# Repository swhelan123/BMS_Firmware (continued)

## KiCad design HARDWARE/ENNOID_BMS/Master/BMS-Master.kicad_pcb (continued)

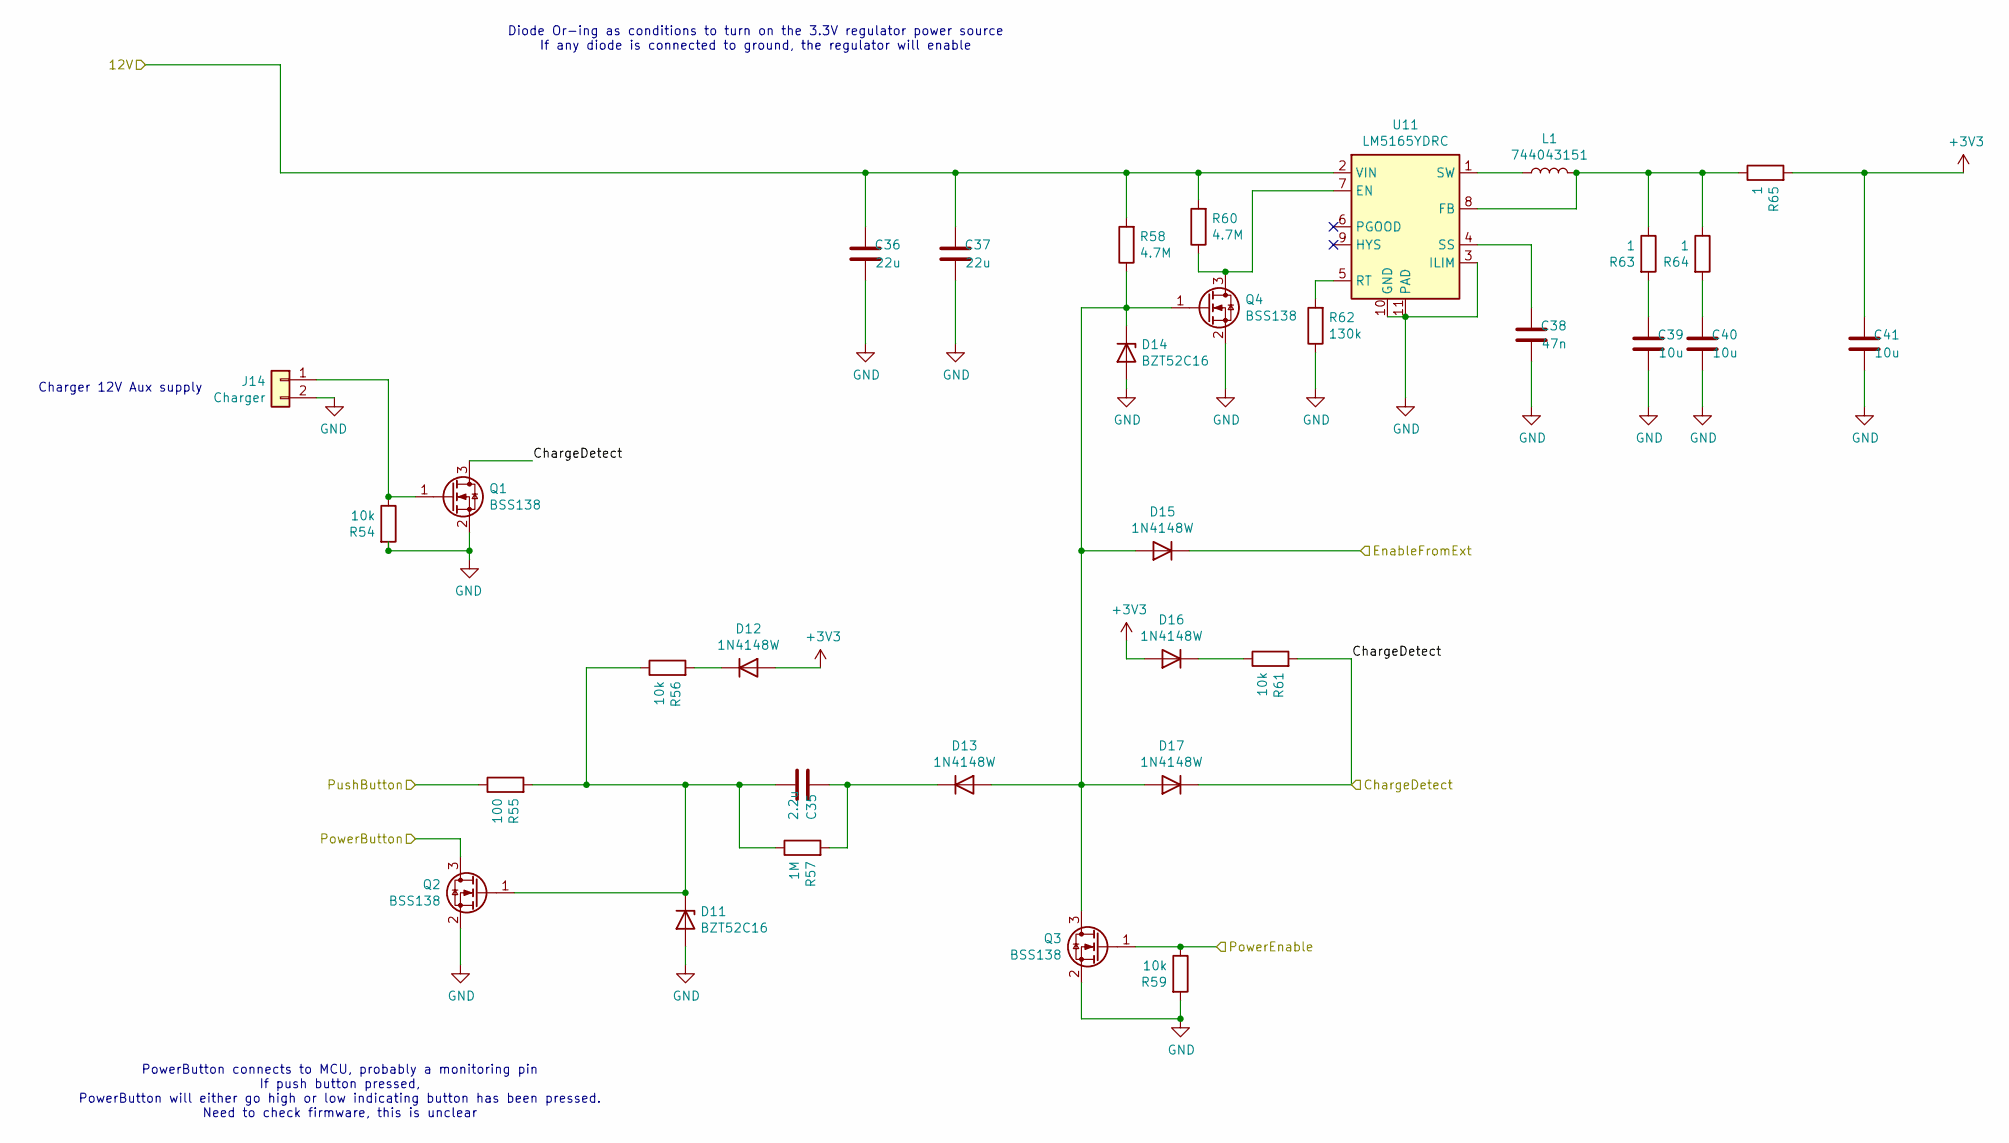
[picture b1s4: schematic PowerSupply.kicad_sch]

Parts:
C35: 2.2u; C_0603_1608Metric; MPN GRM188R61A225KE34D
C36, C37: 22u; C_0805_2012Metric; MPN CL21A226MOQNNNE
C38: 47n; C_0603_1608Metric; Voltage 100V; MPN GCM188R71H473KA55D
C39, C40, C41: 10u; C_0603_1608Metric; MPN CL10A106MQ8NNNC
D11, D14: BZT52C16; D_SOD-123; MPN BZT52C16-E3-08
D12, D13, D15, D16, D17: 1N4148W; D_SOD-123; MPN 1N4148W-7-F
J14: Charger; JST_XH_B2B-XH-A_1x02_P2.50mm_Vertical; MPN B2B-XH-A
L1: 744043151; L_Wuerth_WE-PD2-Typ-MS; MPN 744043151
Q1, Q2, Q3, Q4: BSS138; SOT-23; MPN BSS138
R54, R56, R59, R61: 10k; R_0603_1608Metric; MPN RC0603FR-0710KL
R55: 100; R_0603_1608Metric; MPN RC0603FR-07100RL
R57: 1M; R_0603_1608Metric; MPN RC0603JR-071ML
R58, R60: 4.7M; R_0603_1608Metric; MPN RC0603FR-074M7L
R62: 130k; R_0603_1608Metric; MPN RC0603FR-07130KL
R63, R64, R65: 1; R_0603_1608Metric; MPN RC0603FR-071RL
U11: LM5165YDRC; Texas_S-PVSON-N10_ThermalVias; MPN LM5165YDRCT

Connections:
+3V3: C41.2, D12.2 (A), D16.2 (A), R65.2; also elsewhere on the board
+12V: C36.2, C37.2, R58.2, R60.2, U11.2 (VIN); also elsewhere on the board
/CAN/EnableRequest: D15.1 (K); also elsewhere on the board
/MCU/PowerButton: Q2.3 (D); also elsewhere on the board
/MCU/PowerEnable: Q3.1 (G), R59.1; also elsewhere on the board
/PowerSupply/ChargeDetect: D17.1 (K), Q1.3 (D), R61.2; also elsewhere on the board
/PowerSupply/PushButton: R55.1; also elsewhere on the board
GND: C36.1, C37.1, C38.1, C39.1, C40.1, C41.1, D11.2 (A), D14.2 (A), J14.2, Q1.2 (S), Q2.2 (S), Q3.2 (S), Q4.2 (S), R54.2, R59.2, R62.1, U11.3 (ILIM), U11.10 (GND), U11.11 (PAD); also elsewhere on the board
unnamed: C39.2, R63.2
unnamed: C40.2, R64.2
unnamed: C35.1, D11.1 (K), Q2.1 (G), R55.2, R56.1, R57.1
unnamed: D12.1 (K), R56.2
unnamed: D13.2 (A), D14.1 (K), D15.2 (A), D17.2 (A), Q3.3 (D), Q4.1 (G), R58.1
unnamed: C35.2, D13.1 (K), R57.2
unnamed: D16.1 (K), R61.1
unnamed: J14.1, Q1.1 (G), R54.1
unnamed: Q4.3 (D), R60.1, U11.7 (EN)
unnamed: L1.2, R63.1, R64.1, R65.1, U11.8 (FB)
unnamed: R62.2, U11.5 (RT)
unnamed: C38.2, U11.4 (SS)
unnamed: L1.1, U11.1 (SW)

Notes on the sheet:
Diode Or-ing as conditions to turn on the 3.3V regulator power source If any diode is connected to ground, the regulator will enable
PowerButton connects to MCU, probably a monitoring pin If push button pressed, PowerButton will either go high or low indicating button has been pressed. Need to check firmware, this is unclear
Charger 12V Aux supply

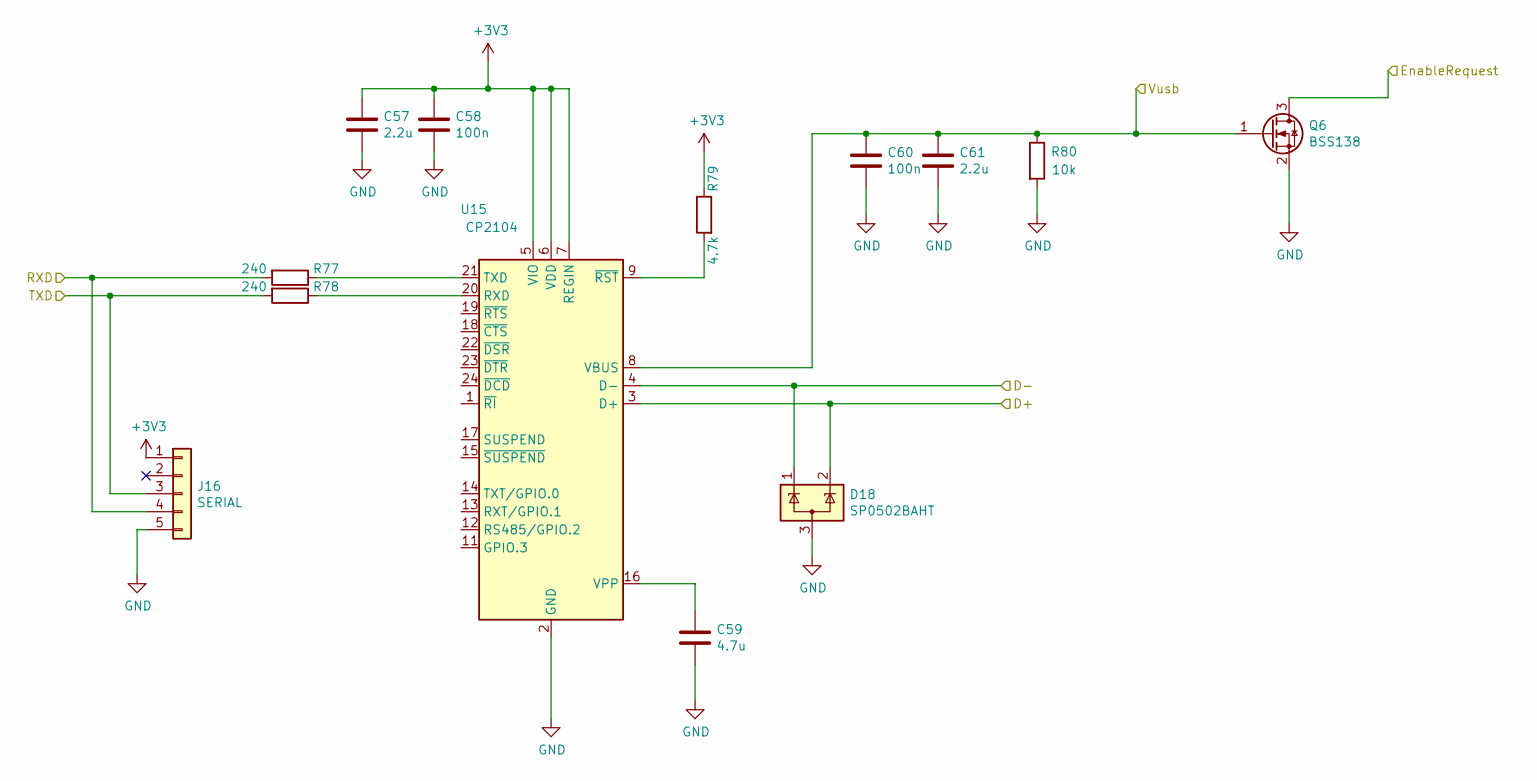
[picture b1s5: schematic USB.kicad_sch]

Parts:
C57, C61: 2.2u; C_0603_1608Metric; MPN GRM188R61A225KE34D
C58, C60: 100n; C_0603_1608Metric; MPN GRM188R71E104KA01D
C59: 4.7u; C_0603_1608Metric; MPN GRM188Z71A475ME15D
D18: SP0502BAHT; SOT-23; MPN SP0502BAHTG
J16: SERIAL; JST_XH_B5B-XH-A_1x05_P2.50mm_Vertical; MPN B5B-XH-A
Q6: BSS138; SOT-23; MPN BSS138
R77, R78: 240; R_0603_1608Metric; MPN RC0603FR-07240RL
R79: 4.7k; R_0603_1608Metric; MPN RC0603JR-074K7L
R80: 10k; R_0603_1608Metric; MPN RC0603FR-0710KL
U15: CP2104; QFN-24-1EP_4x4mm_P0.5mm_EP2.7x2.7mm; MPN CP2104-F03-GM

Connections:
+3V3: C57.1, C58.1, J16.1, R79.1, U15.5 (VIO), U15.6 (VDD), U15.7 (REGIN); also elsewhere on the board
/CAN/EnableRequest: Q6.3 (D); also elsewhere on the board
/MCU/RX_USB: J16.4, R77.2; also elsewhere on the board
/MCU/TX_USB: J16.3, R78.2; also elsewhere on the board
/USB/D+: D18.2 (K), U15.3 (D+); also elsewhere on the board
/USB/D-: D18.1 (K), U15.4 (D-); also elsewhere on the board
/USB/Vusb: C60.1, C61.1, Q6.1 (G), R80.1, U15.8 (VBUS); also elsewhere on the board
GND: C57.2, C58.2, C59.2, C60.2, C61.2, D18.3 (A), J16.5, Q6.2 (S), R80.2, U15.2 (GND), U15.25 (GND); also elsewhere on the board
unnamed: R78.1, U15.20 (RXD)
unnamed: R77.1, U15.21 (TXD)
unnamed: C59.1, U15.16 (VPP)
unnamed: R79.2, U15.9 (~RST)

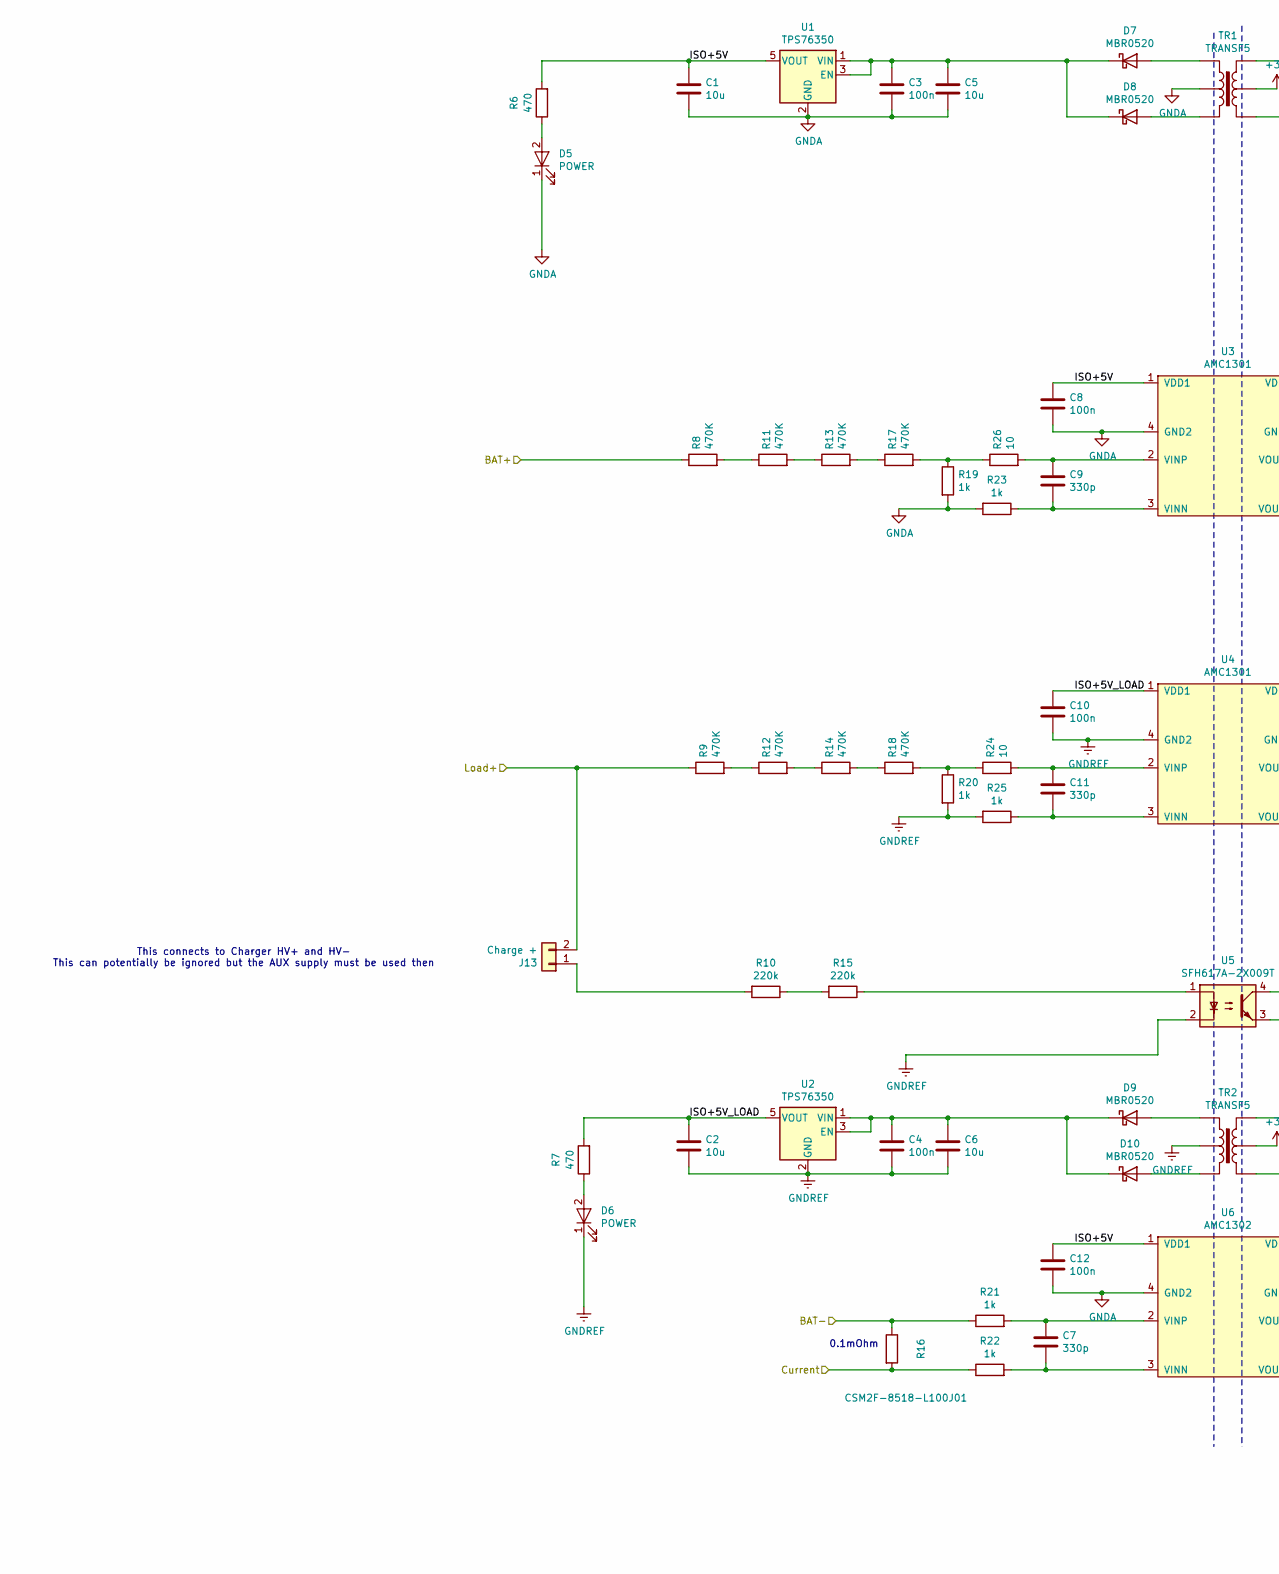
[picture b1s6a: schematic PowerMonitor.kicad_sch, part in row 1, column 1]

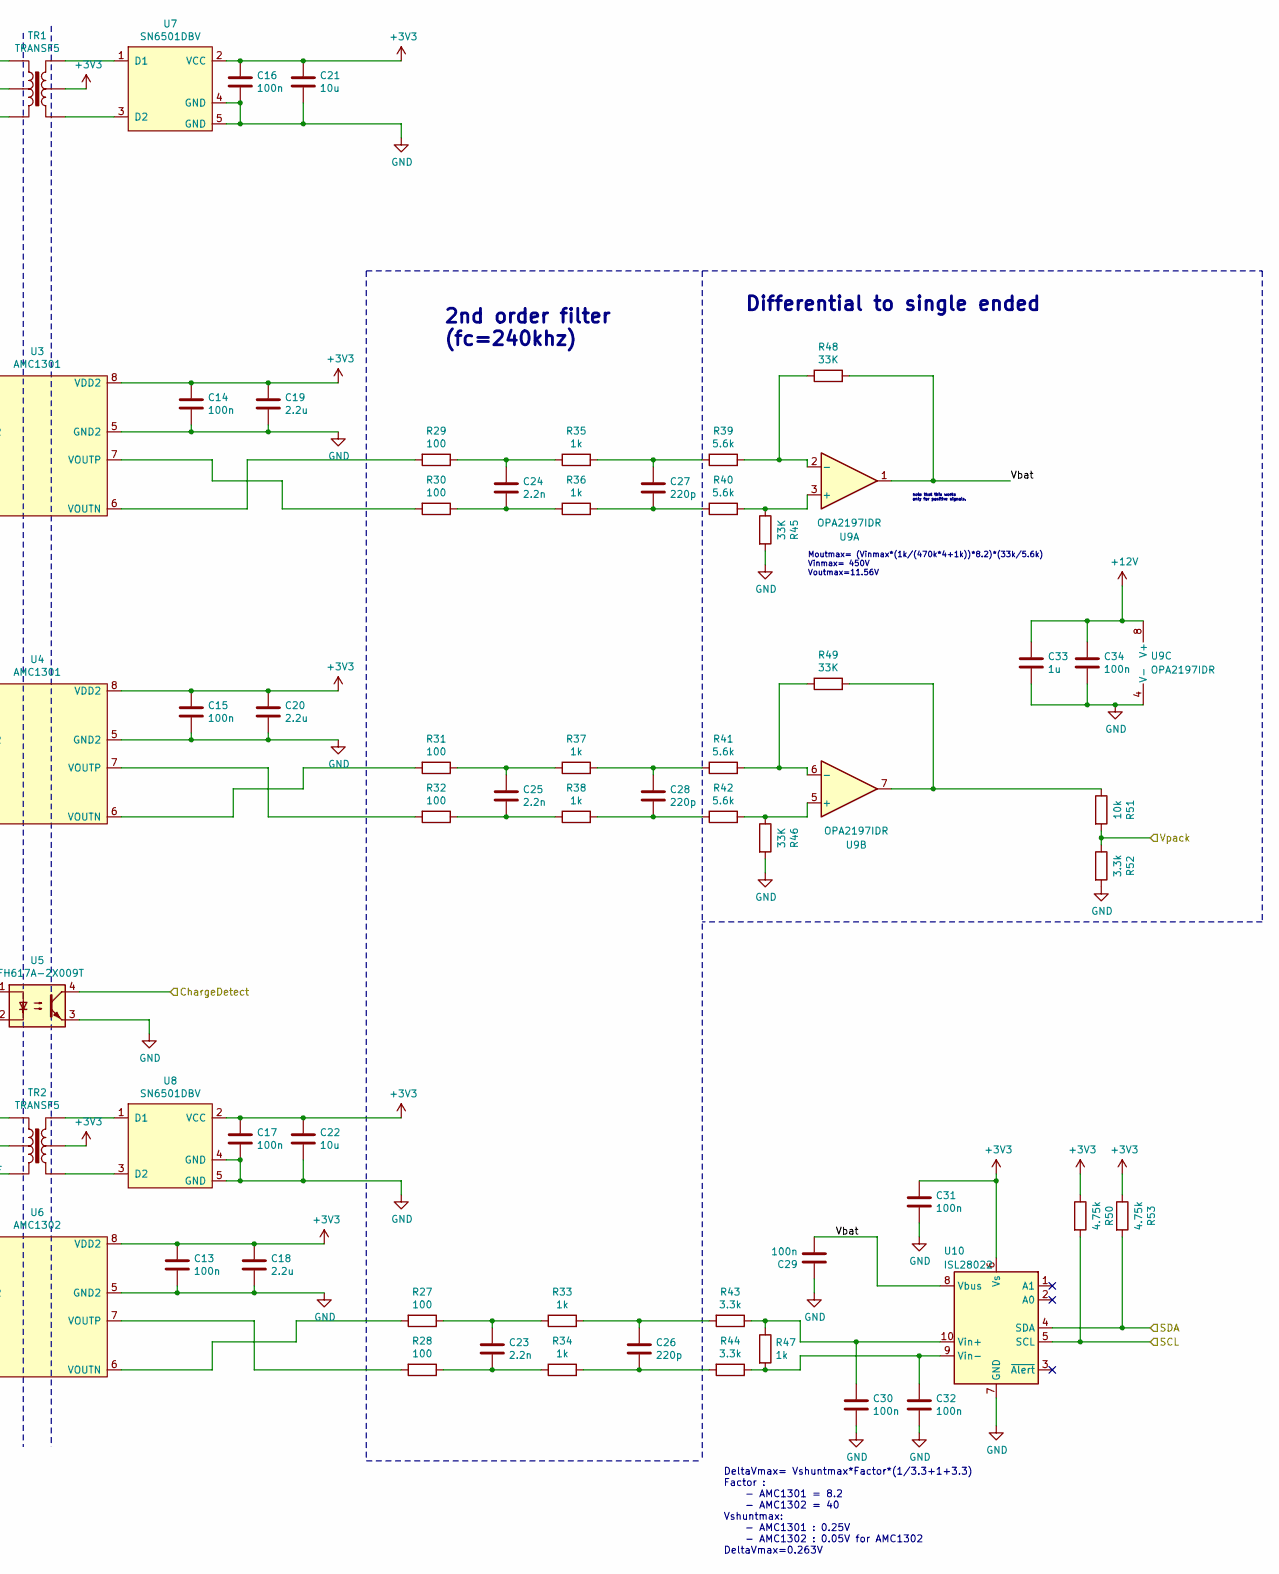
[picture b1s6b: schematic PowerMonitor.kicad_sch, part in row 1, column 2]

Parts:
C1, C2, C5, C6: 10u; C_0805_2012Metric; MPN CL21A106KAYNNNE
C3, C4, C8, C10, C12, C13, C14, C15, C16, C17, C29, C30, C31, C32, C34: 100n; C_0603_1608Metric; MPN GRM188R71E104KA01D
C7, C9, C11: 330p; C_0603_1608Metric; MPN CL10B331KB8NNNC
C18, C19, C20: 2.2u; C_0603_1608Metric; MPN GRM188R61A225KE34D
C21, C22: 10u; C_0603_1608Metric; MPN CL10A106MQ8NNNC
C23, C24, C25: 2.2n; C_0603_1608Metric; MPN GRM1885C1H222JA01D
C26, C27, C28: 220p; C_0603_1608Metric; MPN GRM1555C1H221JA01D
C33: 1u; C_0603_1608Metric; MPN GRM188R71E105KA12D
D5, D6: POWER; LED_0603_1608Metric; MPN SML-D12P8WT86C
D7, D8, D9, D10: MBR0520; D_SOD-123; MPN MBR0502L
J13: Charge +; Phoenix_1x2_1729128; MPN 1729128
R6, R7: 470; R_0603_1608Metric; MPN RC0603JR-07470RL
R8, R9, R11, R12, R13, R14, R17, R18: 470K; R_1206_3216Metric; MPN RC1206FR-07470KL
R10, R15: 220k; R_2512_6332Metric; MPN CRCW2512220KFKEG
R16: CSM2F-8518-L100J01; MPN CSM2F-8518-L100J01
R19, R20, R21, R22, R23, R25, R33, R34, R35, R36, R37, R38, R47: 1k; R_0603_1608Metric; MPN MCWR06X1001FTL
R24, R26: 10; R_0603_1608Metric; MPN RC0603JR-0710RL
R27, R28, R29, R30, R31, R32: 100; R_0603_1608Metric; MPN RC0603FR-07100RL
R39, R40, R41, R42: 5.6k; R_0603_1608Metric; MPN RC0603JR-075K6L
R43, R44, R52: 3.3k; R_0603_1608Metric; MPN RC0603FR-073K3L
R45, R46, R48, R49: 33K; R_0603_1608Metric; MPN RC0603FR-0733KL
R50, R53: 4.75k; R_0603_1608Metric; MPN RC0603JR-074K7L
R51: 10k; R_0603_1608Metric; MPN RC0603FR-0710KL
TR1, TR2: TRANSF5; WURTH-760390014; MPN 760390014
U1, U2: TPS76350; SOT-23-5; MPN TPS76350DBVR
U3, U4: AMC1301; SSO-8_6.8x5.9mm_Pitch1.27mm_Clearance8mm; MPN AMC1301DWV
U5: SFH617A-2X009T; SMDIP-4_W9.53mm_Clearance8mm; MPN SFH617A-2X009T
U6: AMC1302; SSO-8_6.8x5.9mm_Pitch1.27mm_Clearance8mm; MPN AMC1302
U7, U8: SN6501DBV; SOT-23-5; MPN SN6501DBVR
U9: OPA2197IDR; SOIC-8_3.9x4.9mm_P1.27mm; MPN OPA2197IDR
U10: ISL28022; MSOP-10_3x3mm_P0.5mm; MPN ISL28022FUZ-T7A

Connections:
+3V3: C13.1, C14.1, C15.1, C16.1, C17.1, C18.1, C19.1, C20.1, C21.1, C22.1, C31.2, R50.1, R53.1, TR1.5, TR2.5, U3.8 (VDD2), U4.8 (VDD2), U6.8 (VDD2), U7.2 (VCC), U8.2 (VCC), U10.6 (Vs); also elsewhere on the board
+12V: C33.1, C34.1, U9.8 (V+); also elsewhere on the board
/BAT+: R8.1; also elsewhere on the board
/Load+: J13.2, R9.1; also elsewhere on the board
/MCU/SCL: R50.2, U10.5 (SCL); also elsewhere on the board
/MCU/SDA: R53.2, U10.4 (SDA); also elsewhere on the board
/MCU/Vpack: R51.2, R52.1; also elsewhere on the board
/PowerMonitor/Current: R16.2, R22.1; also elsewhere on the board
/PowerMonitor/ISO+5V: C1.1, C8.1, C12.1, R6.2, U1.5 (VOUT), U3.1 (VDD1), U6.1 (VDD1)
/PowerMonitor/ISO+5V_LOAD: C2.1, C10.1, R7.2, U2.5 (VOUT), U4.1 (VDD1)
/PowerMonitor/Vbat: C29.1, R48.2, U9.1, U10.8 (Vbus)
/PowerSupply/ChargeDetect: U5.4; also elsewhere on the board
GND: C13.2, C14.2, C15.2, C16.2, C17.2, C18.2, C19.2, C20.2, C21.2, C22.2, C29.2, C30.1, C31.1, C32.1, C33.2, C34.2, R45.2, R46.2, R52.2, U3.5 (GND2), U4.5 (GND2), U5.3, U6.5 (GND2), U7.4 (GND), U7.5 (GND), U8.4 (GND), U8.5 (GND), U9.4 (V-), U10.7 (GND); also elsewhere on the board
GNDA: C1.2, C3.2, C5.2, C8.2, C12.2, D5.1 (K), R16.1, R19.2, R21.1, R23.2, TR1.2, U1.2 (GND), U3.4 (GND2), U6.4 (GND2); also elsewhere on the board
GNDREF: C2.2, C4.2, C6.2, C10.2, D6.1 (K), R20.2, R25.2, TR2.2, U2.2 (GND), U4.4 (GND2), U5.2; also elsewhere on the board
unnamed: C23.1, R27.1, R33.1
unnamed: C23.2, R28.1, R34.1
unnamed: C24.1, R29.1, R35.1
unnamed: C24.2, R30.1, R36.1
unnamed: C25.1, R31.1, R37.1
unnamed: C25.2, R32.1, R38.1
unnamed: C26.1, R33.2, R43.2
unnamed: C26.2, R34.2, R44.2
unnamed: C27.1, R35.2, R39.1
unnamed: C27.2, R36.2, R40.1
unnamed: C28.1, R37.2, R41.1
unnamed: C28.2, R38.2, R42.1
unnamed: D5.2 (A), R6.1
unnamed: D6.2 (A), R7.1
unnamed: D7.2 (A), TR1.1
unnamed: C3.1, C5.1, D7.1 (K), D8.1 (K), U1.1 (VIN), U1.3 (EN)
unnamed: D8.2 (A), TR1.3
unnamed: D9.2 (A), TR2.1
unnamed: D10.2 (A), TR2.3
unnamed: C4.1, C6.1, D9.1 (K), D10.1 (K), U2.1 (VIN), U2.3 (EN)
unnamed: J13.1, R10.2
unnamed: R10.1, R15.2
unnamed: R8.2, R11.1
unnamed: R11.2, R13.1
unnamed: R9.2, R12.1
unnamed: R12.2, R14.1
unnamed: R13.2, R17.1
unnamed: R14.2, R18.1
unnamed: R15.1, U5.1
unnamed: R17.2, R19.1, R26.1
unnamed: R18.2, R20.1, R24.1
unnamed: R49.2, R51.1, U9.7
unnamed: C9.2, R23.1, U3.3 (VINN)
unnamed: C9.1, R26.2, U3.2 (VINP)
unnamed: R29.2, U3.6 (VOUTN)
unnamed: R30.2, U3.7 (VOUTP)
unnamed: C11.2, R25.1, U4.3 (VINN)
unnamed: C11.1, R24.2, U4.2 (VINP)
unnamed: R31.2, U4.6 (VOUTN)
unnamed: R32.2, U4.7 (VOUTP)
unnamed: C7.2, R22.2, U6.3 (VINN)
unnamed: C7.1, R21.2, U6.2 (VINP)
unnamed: R27.2, U6.6 (VOUTN)
unnamed: R28.2, U6.7 (VOUTP)
unnamed: TR1.6, U7.1 (D1)
unnamed: TR1.4, U7.3 (D2)
unnamed: TR2.6, U8.1 (D1)
unnamed: TR2.4, U8.3 (D2)
unnamed: R40.2, R45.1, U9.3 (+)
unnamed: R39.2, R48.1, U9.2 (-)
unnamed: R42.2, R46.1, U9.5 (+)
unnamed: R41.2, R49.1, U9.6 (-)
unnamed: C30.2, R43.1, R47.1, U10.10 (Vin+)
unnamed: C32.2, R44.1, R47.2, U10.9 (Vin-)

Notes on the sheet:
Moutmax= (Vinmax*(1k/(470k*4+1k))*8.2)*(33k/5.6k) Vinmax= 450V Voutmax=11.56V
0.1mOhm
note that this works only for positive signals.
Differential to single ended
This connects to Charger HV+ and HV- This can potentially be ignored but the AUX supply must be used then
DeltaVmax= Vshuntmax*Factor*(1/3.3+1+3.3) Factor : - AMC1301 = 8.2 - AMC1302 = 40 Vshuntmax: - AMC1301 : 0.25V - AMC1302 : 0.05V for AMC1302 DeltaVmax=0.263V
2nd order filter (fc=240khz)

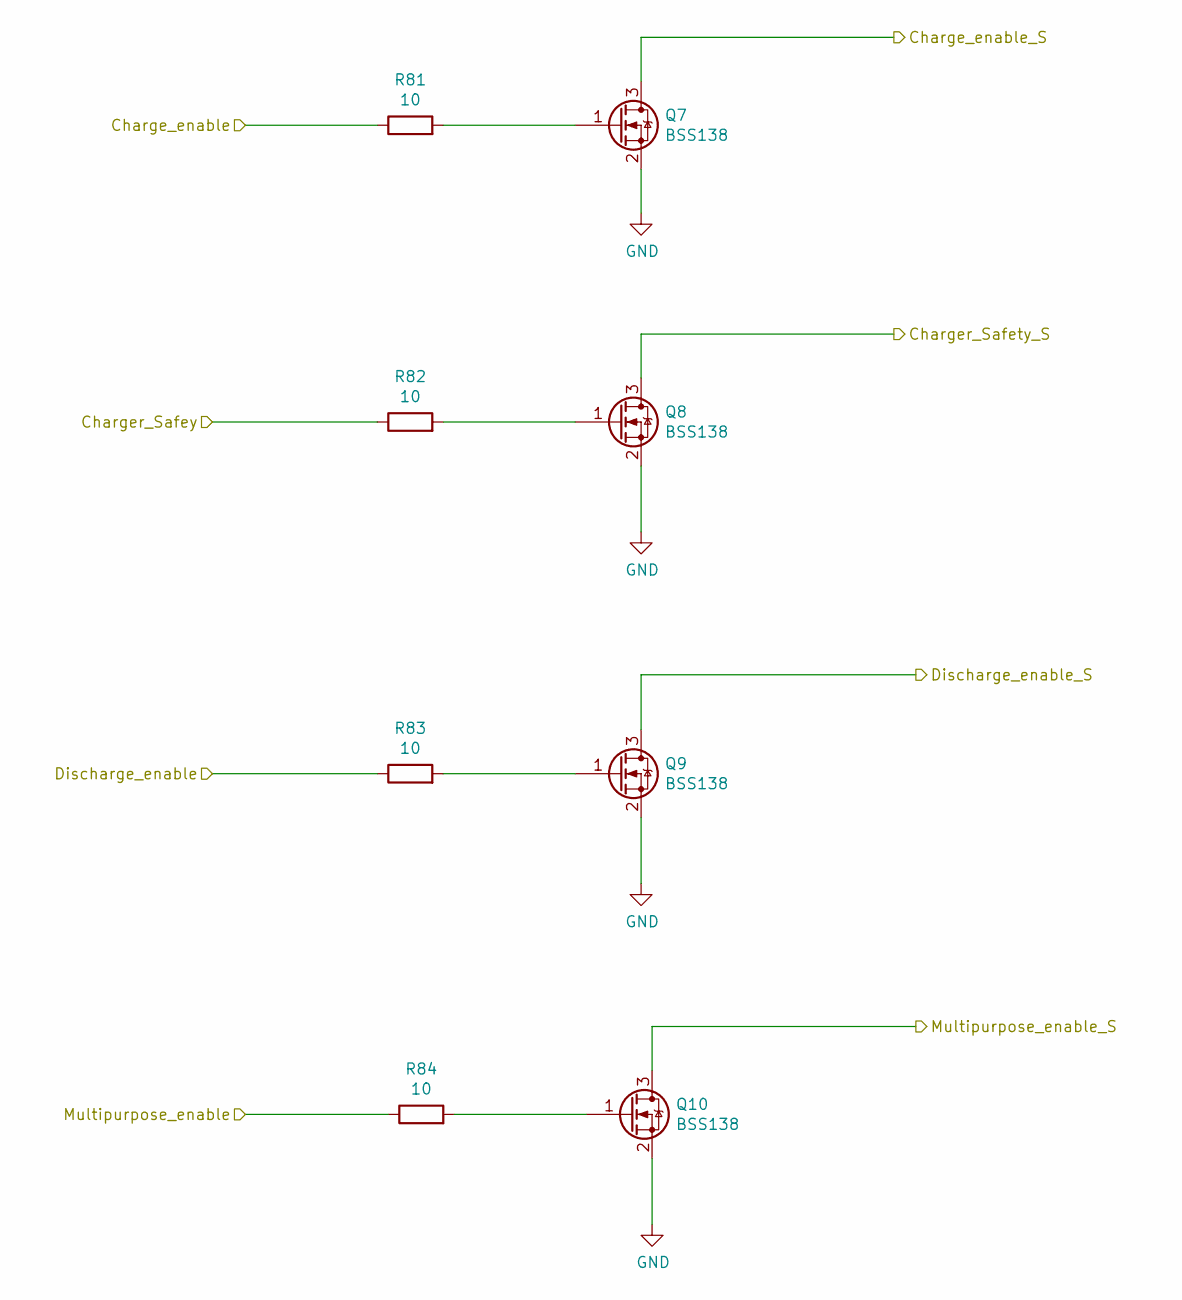
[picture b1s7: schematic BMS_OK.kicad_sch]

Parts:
Q7, Q8, Q9, Q10: BSS138; SOT-23; MPN BSS138
R81, R82, R83, R84: 10; R_0603_1608Metric; MPN RC0603JR-0710RL

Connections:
/BMS_OK/Charge_enable: R81.1; also elsewhere on the board
/BMS_OK/Charge_enable_S: Q7.3 (D); also elsewhere on the board
/BMS_OK/Charger_Safety_S: Q8.3 (D); also elsewhere on the board
/BMS_OK/Charger_Safey: R82.1; also elsewhere on the board
/BMS_OK/Discharge_enable: R83.1; also elsewhere on the board
/BMS_OK/Discharge_enable_S: Q9.3 (D); also elsewhere on the board
/BMS_OK/Multipurpose_enable: R84.1; also elsewhere on the board
/BMS_OK/Multipurpose_enable_S: Q10.3 (D); also elsewhere on the board
GND: Q7.2 (S), Q8.2 (S), Q9.2 (S), Q10.2 (S); also elsewhere on the board
unnamed: Q7.1 (G), R81.2
unnamed: Q8.1 (G), R82.2
unnamed: Q9.1 (G), R83.2
unnamed: Q10.1 (G), R84.2

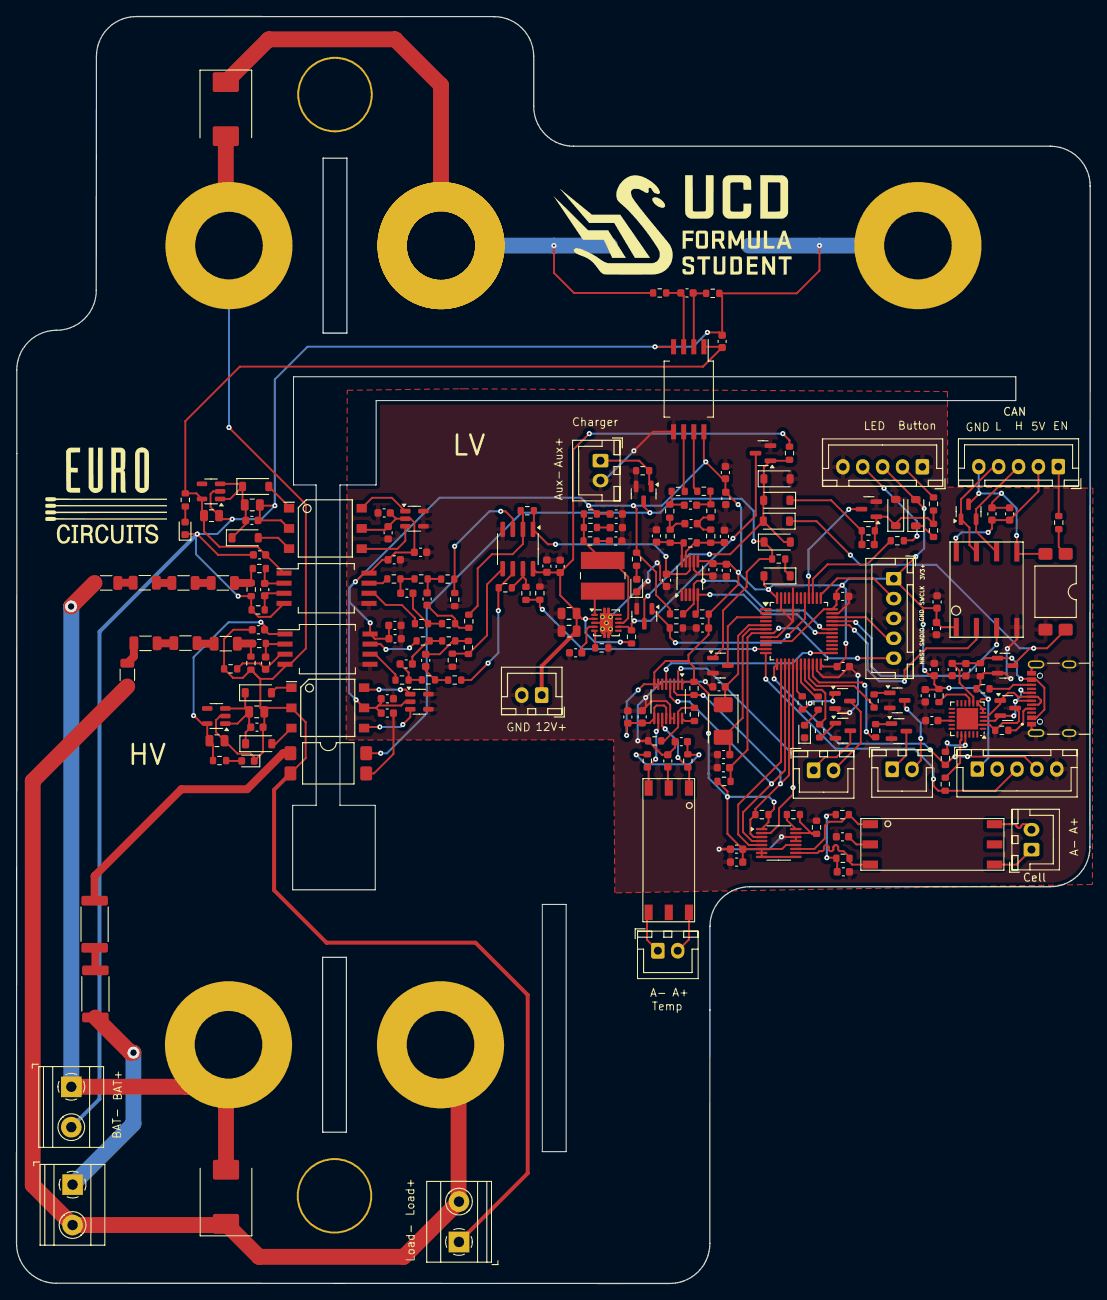
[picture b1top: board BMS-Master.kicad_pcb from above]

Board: 2 copper layers, 135.1 x 159.4 mm, 218 parts (1 on the bottom side), 149 nets.

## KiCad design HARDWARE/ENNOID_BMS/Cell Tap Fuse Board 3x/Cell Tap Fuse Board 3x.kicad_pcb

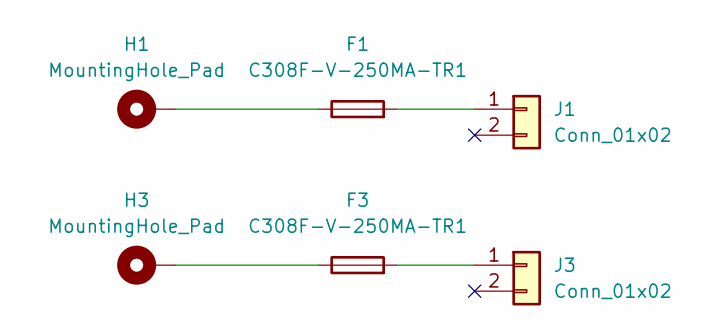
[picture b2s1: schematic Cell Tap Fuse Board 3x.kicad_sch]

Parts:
F1, F3: C308F-V-250MA-TR1; MPN C308F-V-250MA-TR1
H1, H3: MountingHole_Pad; MountingHole_5.5mm_Pad
J1, J3: Conn_01x02; Molex_PicoBlade_53047-0210_1x02_P1.25mm_Vertical; MPN 53047-0210

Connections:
unnamed: F1.1, H1.1
unnamed: F3.1, H3.1
unnamed: F1.2, J1.1
unnamed: F3.2, J3.1

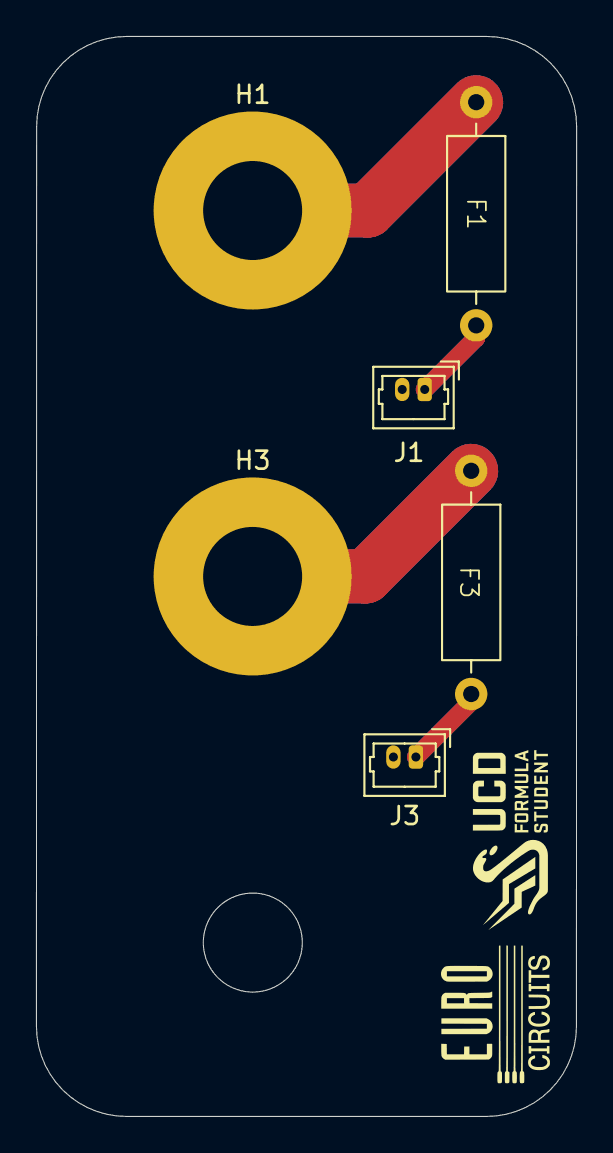
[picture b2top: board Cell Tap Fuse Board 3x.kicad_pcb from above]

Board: 2 copper layers, 30.0 x 60.0 mm, 6 parts (0 on the bottom side), 4 nets.

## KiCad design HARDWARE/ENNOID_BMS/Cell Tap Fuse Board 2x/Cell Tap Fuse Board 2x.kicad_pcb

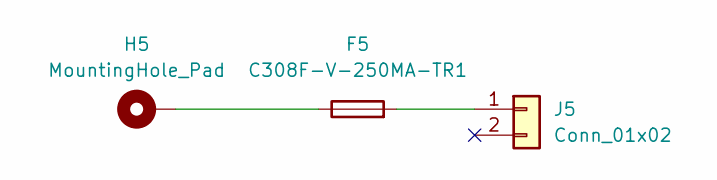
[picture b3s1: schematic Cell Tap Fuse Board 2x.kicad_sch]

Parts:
F5: C308F-V-250MA-TR1; MPN C308F-V-250MA-TR1
H5: MountingHole_Pad; MountingHole_5.5mm_Pad
J5: Conn_01x02; Molex_PicoBlade_53047-0210_1x02_P1.25mm_Vertical; MPN 53047-0210

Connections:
unnamed: F5.1, H5.1
unnamed: F5.2, J5.1

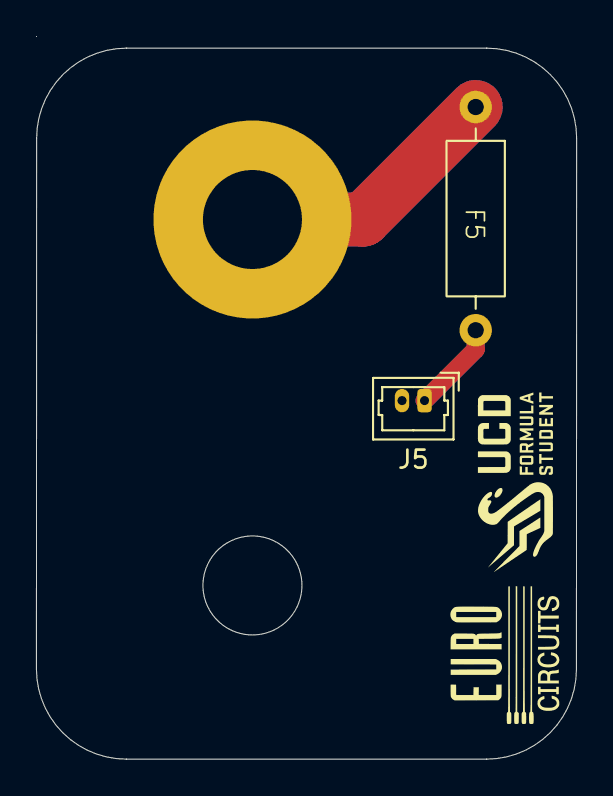
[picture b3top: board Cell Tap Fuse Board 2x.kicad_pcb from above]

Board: 2 copper layers, 30.0 x 40.1 mm, 3 parts (0 on the bottom side), 2 nets.
